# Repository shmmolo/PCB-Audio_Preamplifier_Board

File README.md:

# Audio Preamplifier Board (Active Baxandall)

A stereo audio preamplifier with active Baxandall tone control and NE5532 op-amp for low-noise, high-fidelity performance.

## Features
- Stereo AUX input (3.5 mm jack)
- Active Baxandall bass and treble control
- ±12 V supply using LM317/LM337 power source
- Dual-ganged potentiometers for Bass, Treble, and Volume
- NE5532 dual op-amp for both channels

## Performance
| Parameter | Typical Value |
|------------|----------------|
| Bass Boost/Cut | ±15 dB @ 100 Hz |
| Treble Boost/Cut | ±14 dB @ 10 kHz |
| Slew Rate (NE5532) | 9 V/µs |
| THD | 0.0005 % |
| Bandwidth | 10 MHz |
| Supply Voltage | ±12 V |

## Applications
- Stereo preamp or tone control
- Signal conditioning for amplifiers
- DIY audio and analog circuit experimentation

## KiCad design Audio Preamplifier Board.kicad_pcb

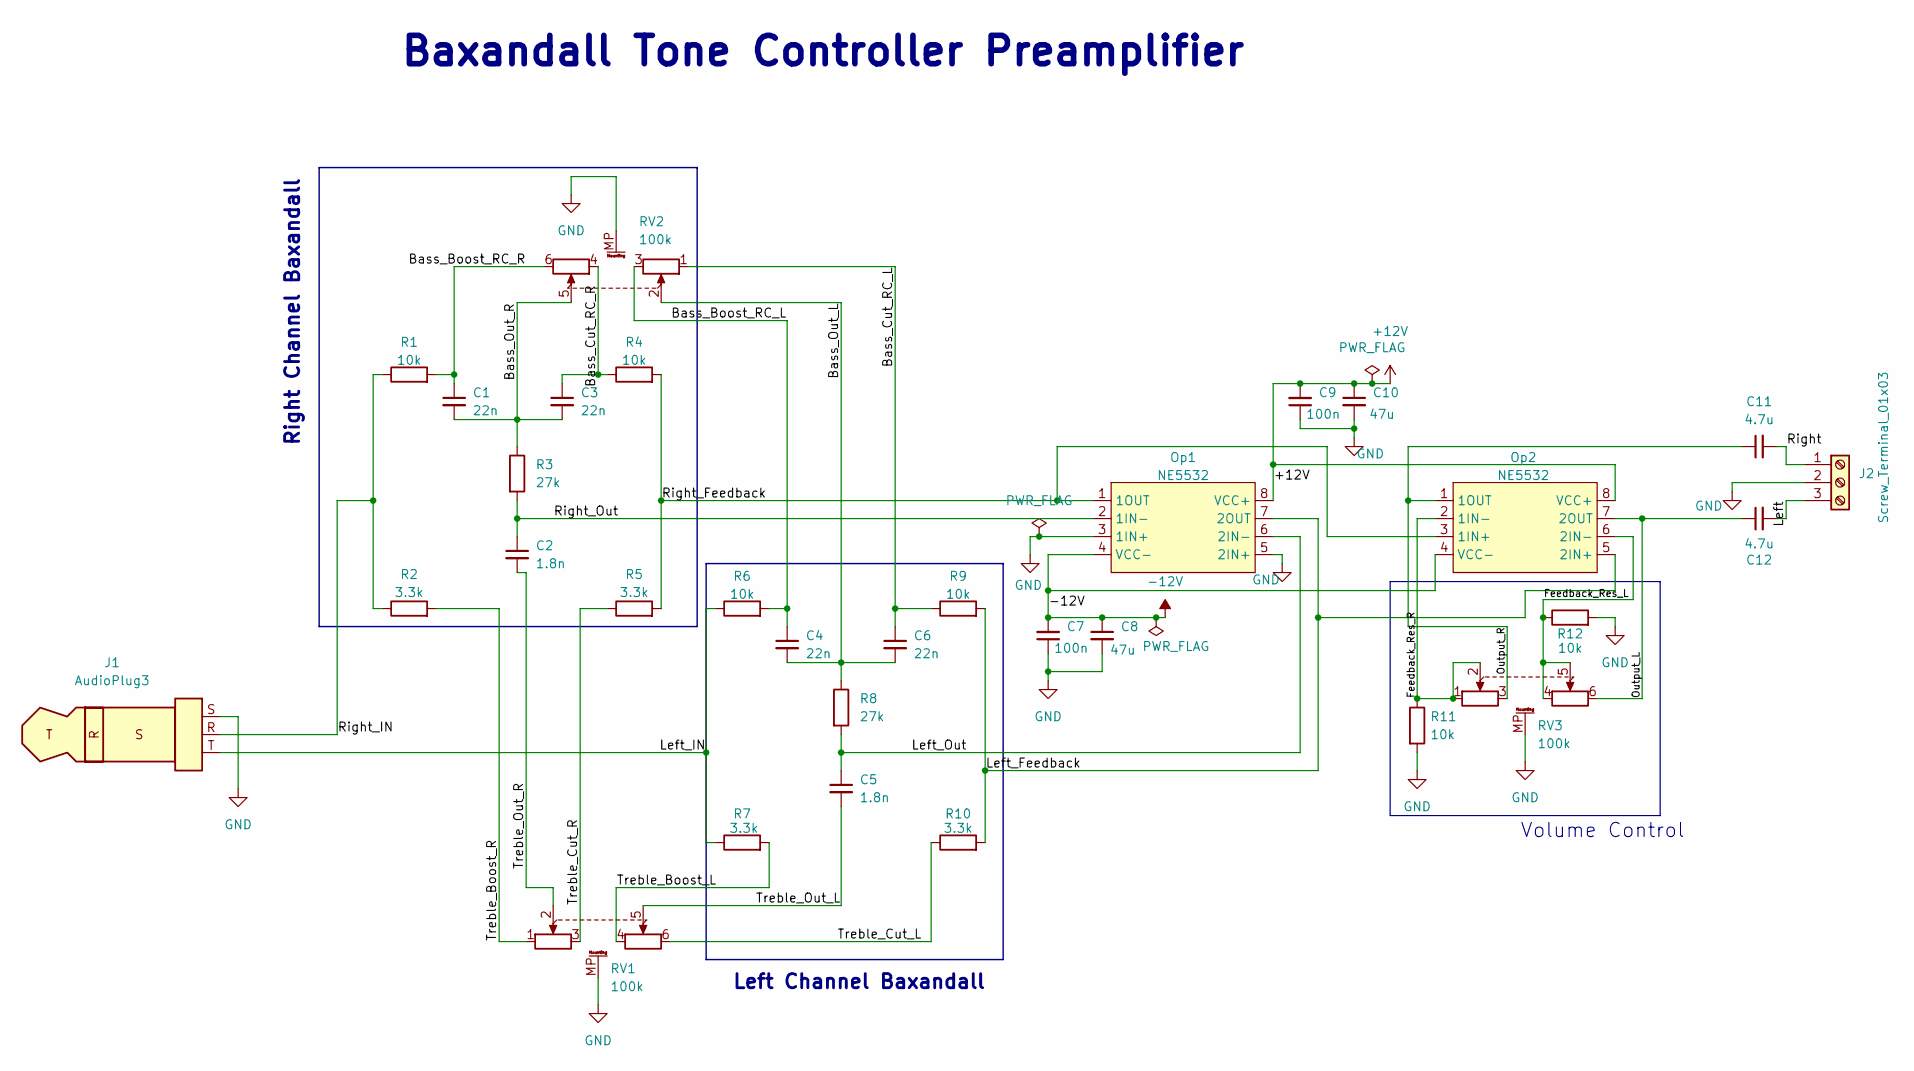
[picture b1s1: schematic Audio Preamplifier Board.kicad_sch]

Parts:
C1, C3, C4, C6: 22n; C_Disc_D4.7mm_W2.5mm_P5.00mm
C2, C5: 1.8n; C_Disc_D4.7mm_W2.5mm_P5.00mm
C7, C9: 100n; C_Disc_D4.7mm_W2.5mm_P5.00mm
C8, C10: 47u; CP_Radial_D8.0mm_P3.50mm
C11, C12: 4.7u; CP_Radial_D8.0mm_P3.50mm
J1: AudioPlug3; Jack_3.5mm_CUI_SJ1-3533NG_Horizontal
J2: Screw_Terminal_01x03; TerminalBlock_Phoenix_MKDS-1,5-3-5.08_1x03_P5.08mm_Horizont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
Op1, Op2: NE5532
R1, R4, R6, R9, R11, R12: 10k; R_Axial_DIN0207_L6.3mm_D2.5mm_P7.62mm_Horizontal
R2, R5, R7, R10: 3.3k; R_Axial_DIN0207_L6.3mm_D2.5mm_P7.62mm_Horizontal
R3, R8: 27k; R_Axial_DIN0207_L6.3mm_D2.5mm_P7.62mm_Horizontal
RV1, RV2, RV3: 100k; Potentiometer_Alps_RK163_Dual_Horizontal

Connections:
+12V: C9.2, C10.1, Op1.8 (VCC+), Op2.8 (VCC+)
-12V: C7.2, C8.1, Op1.4 (VCC-), Op2.4 (VCC-)
/Bass_Boost_RC_L: C4.1, R6.2, RV2.3
/Bass_Boost_RC_R: C1.1, R1.2, RV2.6
/Bass_Cut_RC_L: C6.1, R9.1, RV2.1
/Bass_Cut_RC_R: C3.1, R4.1, RV2.4
/Bass_Out_L: C4.2, C6.2, R8.1, RV2.2
/Bass_Out_R: C1.2, C3.2, R3.1, RV2.5
/Feedback_Res_L: Op2.6 (2IN-), R12.1, RV3.4, RV3.5
/Feedback_Res_R: Op2.2 (1IN-), R11.1, RV3.1, RV3.2
/Left: C12.2, J2.3
/Left_Feedback: Op1.7 (2OUT), Op2.5 (2IN+), R9.2, R10.2
/Left_IN: J1.T, R6.1, R7.1
/Left_Out: C5.1, Op1.6 (2IN-), R8.2
/Output_L: C12.1, Op2.7 (2OUT), RV3.6
/Output_R: C11.1, Op2.1 (1OUT), RV3.3
/Right: C11.2, J2.1
/Right_Feedback: Op1.1 (1OUT), Op2.3 (1IN+), R4.2, R5.2
/Right_IN: J1.R, R1.1, R2.1
/Right_Out: C2.1, Op1.2 (1IN-), R3.2
/Treble_Boost_L: R7.2, RV1.4
/Treble_Boost_R: R2.2, RV1.1
/Treble_Cut_L: R10.1, RV1.6
/Treble_Cut_R: R5.1, RV1.3
/Treble_Out_L: C5.2, RV1.5
/Treble_Out_R: C2.2, RV1.2
GND: C7.1, C8.2, C9.1, C10.2, J1.S, J2.2, Op1.3 (1IN+), Op1.5 (2IN+), R11.2, R12.2, RV1.MP (MountPin), RV2.MP (MountPin), RV3.MP (MountPin)

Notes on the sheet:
Left Channel Baxandall
Right Channel Baxandall
Baxandall Tone Controller Preamplifier
Volume Control

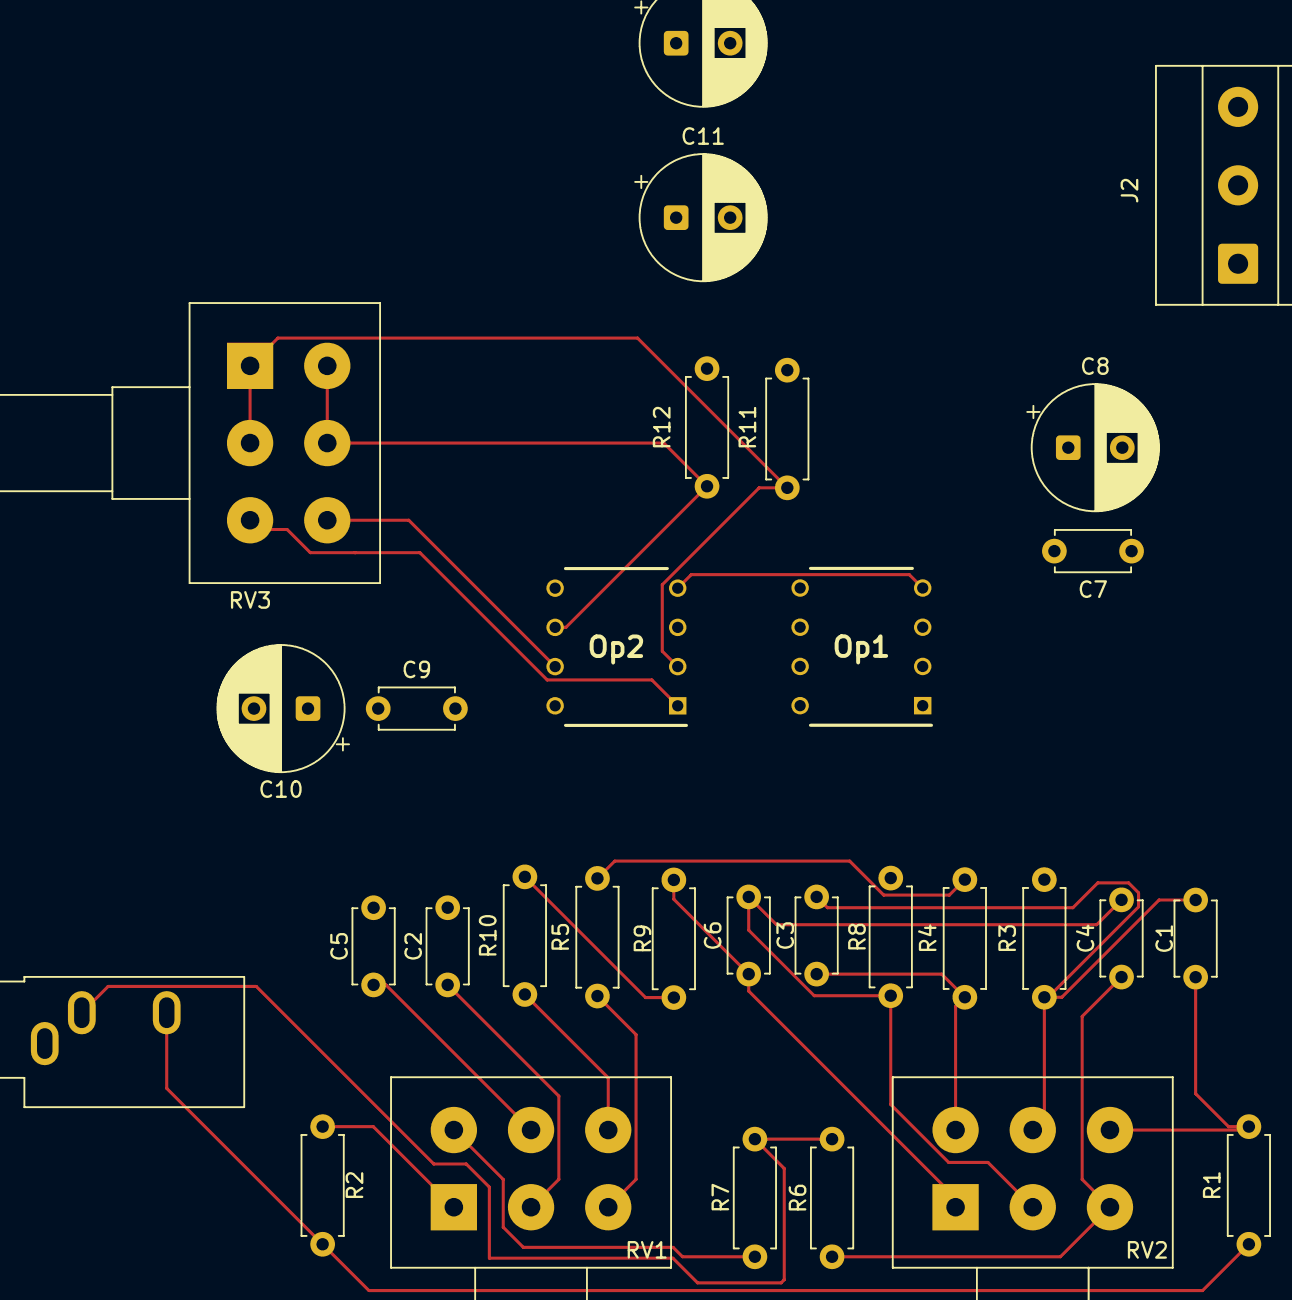
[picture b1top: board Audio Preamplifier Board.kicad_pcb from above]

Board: 2 copper layers, 31 parts (0 on the bottom side), 27 nets.

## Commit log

2025-10-29 README.md
2025-10-29 Added to Hardware
2025-10-29 Added to Docs
